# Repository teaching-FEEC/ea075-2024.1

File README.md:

# EA075 - Introdução ao Projeto de Sistemas Embarcados

1° semestre de 2024

Profa. Paula Dornhofer Paro Costa

⚠️ Não altere este arquivo README.MD

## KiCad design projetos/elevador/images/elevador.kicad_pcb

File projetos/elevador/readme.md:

# Projeto de um circuito de controle para elevadores
# Elevator control circuit project

## Apresentação

O presente projeto foi originado no contexto das atividades da disciplina de graduação *EA075 - Introdução ao Projeto de Sistemas Embarcados*, 
oferecida no primeiro semestre de 2024, na Unicamp, sob supervisão da Profa. Dra. Paula Dornhofer Paro Costa, do Departamento de Engenharia de Computação e Automação (DCA) da Faculdade de Engenharia Elétrica e de Computação (FEEC).

|Nome  | RA | Curso|
|--|--|--|
| André Guilherme da Luz  | 231343  | Eng. Elétrica|
| Gabriel Vianna Serra  | 258555  | Eng. Elétrica|

## Arquivos Importantes

Esquemático -- https://github.com/gaserra/ea075-2024.1/blob/636cf3e964390284290cc4d843cebd671a3fc66c/projetos/elevador/pdf/Esquem%C3%A1tico.pdf

Lista de Componentes -- https://github.com/gaserra/ea075-2024.1/blob/99e6916becb7f16d3520f543a689d3d09d11a9cd/projetos/elevador/componentes.md

PCB -- https://github.com/gaserra/ea075-2024.1/blob/31582293e5f1df663656b3f0aaa58bb34f14db0e/projetos/elevador/pdf/PCI.pdf

## Descrição do Projeto
A ideia do projeto consiste em desenvolver um circuito controlador para elevadores, a fim de tomar decisões como a escolha de que o elevador deve subir, descer ou manter-se no lugar com base no andar atual, prioridade de chamada e situações de segurança, por exemplo. Nosso contexto de concepção desse projeto veio do motivo de que é algo muito útil e presente no dia a dia de pessoas, bem como factível de ser projetado durante o semestre da disciplina, permitindo nos desafiar com as possíveis variáveis de desenvolvimento sem sobrecarregar os esforços dentro do tempo estipulado.

Outro lado positivo do projeto é que seu custo não tende a ser alto, levando em conta que a lógica pode ser desenvolvida sem a necessidade de processamento muito avançado, e os demais dispositivos que podem ser possivelmente usados não tendem a ser caros (alguns sensores e circuitos básicos para mudança de direção do motor). Dessa forma, levando em conta um investimento que requer pouca manutenção (o principal serviço é o software envolvido no controle dos elevadores e o microprocessador do mesmo, que tende a ter boa durabilidade), pouco capital e que proporciona um controle útil e necessário na logística dos elevadores, temos um projeto viável e de custo acessível.

O projeto consiste em um produto já estabelecido no mercado, que visa garantir um transporte vertical eficiente, seguro e confiável, ao mesmo tempo em que buscamos a redução dos custos. O sistema tende a beneficiar tanto prédios residenciais, ocorrendo uma valorização do imóvel, quanto comerciais, ocorrendo uma melhora da produtividade dos funcionários.

## Descrição Funcional

### Funcionalidades
O sistema de controle de elevadores deverá ser capaz de executar as seguintes tarefas:
  - Chamadas do elevador: receber e registrar chamadas de todos os andares do prédio.
  - Registrar as solicitações dentro do elevador.
  - Organizar as chamadas com base em uma fila de prioridade.
  - Gerenciar a abertura e fechamento das portas.
  - Responder imediatamente a situações de emergência.
  - Diagnosticar problemas mecânicos e elétricos.
  - Fornecer feedback aos passageiros sobre o andar que está.    

### Configurabilidade
O sistema possui os seguintes estados:
  - Subindo:
    O elevador está se deslocando para cima, pois recebeu uma chamada de algum andar mais elevado ou algum passageiro solicitou parada em um andar acima.
  - Descendo:
    O elevador está se deslocando para baixo, pois recebeu uma chamada de algum andar ou algum passageiro solicitou parada em um andar abaixo de sua posição.
  - Parado:
    O elevador está em um andar específico.
    - Portas abertas:
      O elevador está parado em um andar específico e com a porta aberta para entrada e saída de passageiros.
    - Portas fechadas:
      O elevador está parado em um andar com as portas fechadas, que ocorre após um tempo específico para entrada e saída dos passageiros e verificação de que não há passageiros se locomovendo pra dentro ou pra fora, bem como verificação de que não há possíveis falhas mecânicas e elétricas.

Ao receber chamadas de andares, o elevador (com portas fechadas) muda para o estado "subindo" ou "descendo", assim como quando o passageiro seleciona o andar desejado. Ao chegar no andar, o elevador muda para o modo "parado", inicialmente de portas fechadas, e rapidamente muda para o modo "portas abertas". Após um determinado tempo para entrarem e saírem passageiros, há a mudança de estado para "portas fechadas" novamente, se as condições de segurança forem satisfeitas. Assim, novas chamadas ocorrem, reiniciando. 
Há algumas mudanças de estado fora do funcionamento padrão. Ao verificar problemas mecânicos ou elétricos ou outras emergências, ele passa automaticamente para o modo "parado". Se está parado devido a problemas de segurança, suas portas podem permanecer abertas ou fechadas de acordo com a ocasião.

### Eventos
Os eventos de mudança de estado:
  - Chamada de um andar (evento não-periódico, passa do estado "parado" para "subindo" ou "descendo").
  - Chegada do elevador a um andar solicitado (evento não-periódico, passa do estado "subindo" ou "descendo" para "parado").
  - Ao parar, abertura das portas (evento não-periódico, passa do estado "parado" para o sub estado "portas abertas").
  - Fechamento das portas após um tempo para entrada e saída de passageiros, bem como garantia de segurança (evento não-periódico, passa do sub estado "portas abertas" para "portas fechadas").
  - Pressionamento do botão de fechada de portas (evento não-periódico, passa do estado "portas abertas" para "portas fechadas").
  - Pessoa entre a porta (evento não-periódico, mantém-se no sub estado "portas abertas").
  - Detecção de falha (evento não-periódico, passa do estado  "subindo" ou "descendo" para "parado").

### Tratamento de Eventos
  - Chamada de um andar:
    Ao receber uma chamada, o sistema deve organizar as chamadas da melhor maneira, de forma que não fique subindo e descendo várias vezes.
  - Chegada do elevador a um andar solicitado:
    Ao chegar em um andar, o sistema deve alinhar corretamente o chão do elevador com o andar.
  - Ao parar, abertura das portas:
    Após o alinhamento correto do chão do elevador e do andar, o sistema deve mandar um sinal para abertura da porta correta.
  - Fechamento das portas após um tempo para entrada e saída de passageiros:
    Após um tempo previamente definido de abertura das portas, o sistema deve enviar um sinal para o fechamento das portas se as condições de segurança forem satisfeitas.
  - Pressionamento do botão de fechada de portas:
    Caso esteja pressionado o botão, o sistema deve enviar um sinal para fechamento da porta.
  - Pessoa entre a porta:
    O sistema, ao detectar que há algo no local de fechamento da porta, deve enviar o sinal para manter a porta aberta ou cancelar o fechamento.
  - Detecção de falha:
    Ao detectar falha, o sistema deve interromper o movimento e ficar parado.

## Descrição Estrutural do Sistema
O sistema se baseia em um fluxo de estados onde definimos se um elevador sobe, desce ou se mantém parado com base nas solicitações internas e externas do elevador, bem como nas condições de segurança que devem ser satisfeitas. O diagrama abaixo retrata melhor os o fluxo de decisões:

Note que o mesmo funciona tanto para uma pessoa que solicita o elevador pelo lado de fora, quanto para alguém que aperta o botão de um andar já dentro do elevador. O diagrama mostra a situação em condições típicas e síncronas de funcionamento, mas haverá também a necessidade de uma verificação assíncrona em casos de falhas durante o trajeto do elevador, onde o mesmo deve parar e acionar suporte/segurança.
A fila também tem um papel importante, conforme explicado na sessão "Especificação de algoritmos", para saber se o elevador sobe ou desce de acordo com a ordem apertada e se para ou não em outro andar no caminho. De forma resumida, após alguma solicitação que entra em uma fila com uma determinada prioridade, a ideia é que o elevador se movimente baseado nessa fila para atender aos chamados.

## Especificações 

### Especificação Estrutural

O projeto possui dois atuadores, ambos motores CC, para controle de abertura e fechamento das portas do elevador e para subir e descer a cabine. O motor utilizado para o deslocamento vertical da cabine apresenta bastante torque, portanto, sua potência é alta. Com isso, a alimentação é feita utilizando um conversor AC/DC RAC20-K, que entrega 48V para alimentação do circuito do motor. O controle do sentido e da velocidade  é feito na saída do retificador utilizando uma ponte H L298N, conectada também ao microcontrolador, que consegue fazer o controle de ambos os motores paralelamente. 

A ideia do controle da parada correta da cabine do elevador é utilizar dois sensores fotoelétricos em cada andar (um para a parte inferior do piso e outro para a parte superior), sendo que o modelo em consideração é o E3Z-F da Omron. Assim, ao passar pelo sensor, o sistema saberá em que andar está a cabine e o momento correto para iniciar a frenagem. Outra importante função desse periférico é estacionar a cabine de forma extremamente precisa, alinhando o piso do elevador com o andar. Com as informações do andar, um display de sete seguimentos mostrará ao passageiro o andar que a cabine está, o modelo utilizado é o D1X8K-14BL. Os dados são enviados como dois bits, que são decodificados pelo 74LS48, e em seguida enviados para o display.

A porta possui quatro sensores de infravermelho, sendo utilizados dois para cada altura pré-determinada, dispostos em ambos os lados da porta. O papel desses sensores é detectar se há algum objeto entre as portas. O modelo escolhido foi o E18-D80NK-N, que possui um alcance de 6 a 80 cm. Quando um objeto for detectado, o sensor envia ao microcontrolador um sinal de nível lógico baixo. Com a leitura do nível lógico, um comando é enviado para o motor manter a porta aberta.

O elevador irá se locomover por quatro andares, assim, teremos quatro push buttons dentro do elevador para o passageiro indicar o destino desejado. Cada andar possuirá um push button para chamar o veículo. Logo, teremos oito no sistema, que, ao serem pressionados, enviam um sinal que será armazenado na memória estruturada em pilha. Na seção de especificação do algoritmo, o modo de funcionamento dos chamados é explicado de forma a otimizar o trajeto do elevador. Cada push bottom será conectado à uma porta GPIO do microcontrolador.

O microcontrolador escolhido para o sistema foi RP2040 desenvolvido pela Raspbarry Pi. A escolha ocorreu devido à quantidade de portas necessárias para todo o controle do sistema, e como o projeto não precisa uma compexidade alta, este microcontrolador atende os requisitos, além de possuir um custo acessível. Para a comunicação serial, a comunicação do tipo I2C foi escolhida, pois não há necessidade de uma alta velocidade de comunicação que vença em detrimento da menor complexidade.

### Especificação de Algoritmos 
Para a gestão de fila dos andares, o projeto se baseia no seguinte fluxograma:

Os eventos relacionados à abertura e ao fechamento de portas, bem como detecção de falha, sobrecarga e pessoa entre as portas são tratados no fluxograma da seção "_Descrição Estrutural do Sistema_", e tais eventos se relacionam diretamente com este acima no que resumimos pela tomada de decisão "Verificações de segurança ok?". Dessa forma, o algoritmo como um todo deve tratar dos dois fluxogramas, sendo que o primeiro diagrama se encaixa dentro do segundo para simplificarmos a visualização.

O microcontrolador apresenta memórias integradas, ROM, Flash e SRAM, que trabalham com palavras de 32 bits. Visto que projetaremos um controle para elevadores com até 4 andares (suficientemente representados por 2 bits), usando 2 sensores de nível por andar (mais 8 bits para monitoramento), e outras funções de controle como abertura das portas, detecção de movimento, etc, estimamos que seria necessário em torno de 16 bits para tal, portanto o microcontrolador satisfaz a demanda, não necessitando da utilização de uma memnória externa.

## Referências
http://www.electrical-knowhow.com/2012/04/elevator-control-system.html

http://fpgaparatodos.com.br/2011/08/04/exemplo-de-exemplo/

https://cpi.com.ar/info_productos/pdf/E3Z-F.pdf

https://www.watelectronics.com/e18-d80nk-adjustable-infrared-sensor/

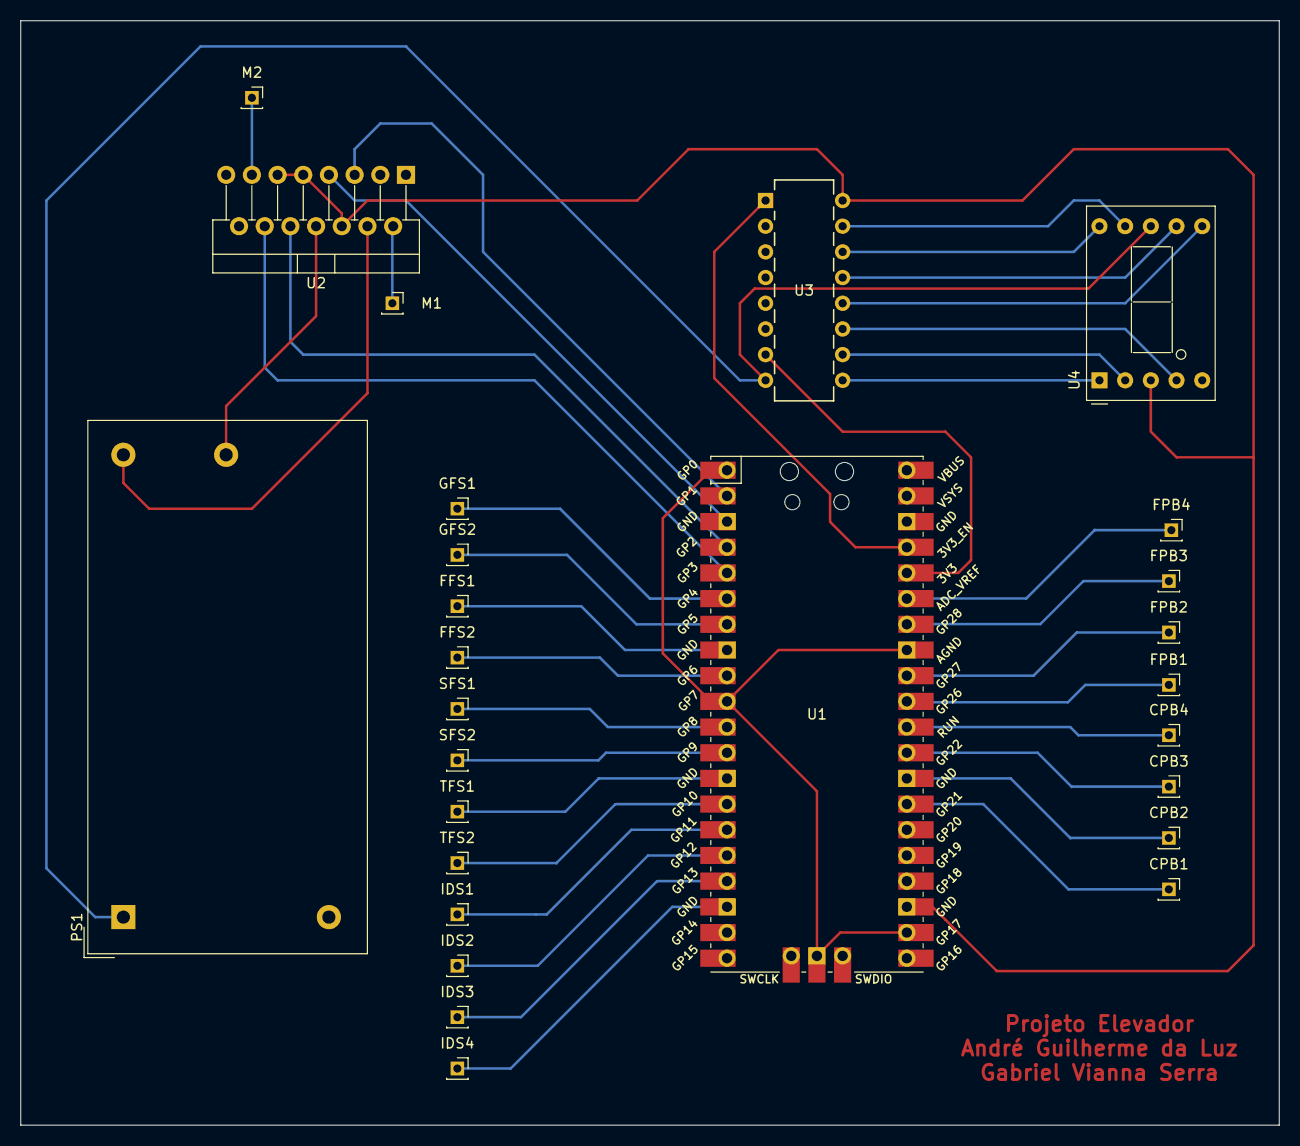
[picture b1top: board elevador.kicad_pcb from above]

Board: 2 copper layers, 124.5 x 109.2 mm, 27 parts (0 on the bottom side), 40 nets.

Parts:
CPB1: Cabin P/B 0; PinSocket_1x01_P2.00mm_Vertical
CPB2: Cabin P/B 1; PinSocket_1x01_P2.00mm_Vertical
CPB3: Cabin P/B 2; PinSocket_1x01_P2.00mm_Vertical
CPB4: Cabin P/B 3; PinSocket_1x01_P2.00mm_Vertical
FFS1: First Floor Sensor 1; PinSocket_1x01_P2.00mm_Vertical
FFS2: First Floor Sensor 2; PinSocket_1x01_P2.00mm_Vertical
FPB1: Floor P/B 0; PinSocket_1x01_P2.00mm_Vertical
FPB2: Floor P/B 1; PinSocket_1x01_P2.00mm_Vertical
FPB3: Floor P/B 2; PinSocket_1x01_P2.00mm_Vertical
FPB4: Floor P/B 3; PinSocket_1x01_P2.00mm_Vertical
GFS1: Ground Floor Sensor 1; PinSocket_1x01_P2.00mm_Vertical
GFS2: Ground Floor Sensor 2; PinSocket_1x01_P2.00mm_Vertical
IDS1: Infrared Door Sensor 1; PinSocket_1x01_P2.00mm_Vertical
IDS2: Infrared Door Sensor 2; PinSocket_1x01_P2.00mm_Vertical
IDS3: Infrared Door Sensor 3; PinSocket_1x01_P2.00mm_Vertical
IDS4: Infrared Door Sensor 4; PinSocket_1x01_P2.00mm_Vertical
M1, M2: Motor_DC; PinSocket_1x01_P2.00mm_Vertical
PS1: RAC20-48SK; Converter_ACDC_Recom_RAC20-xxSK_THT
SFS1: Second Floor Sensor 1; PinSocket_1x01_P2.00mm_Vertical
SFS2: Second Floor Sensor 2; PinSocket_1x01_P2.00mm_Vertical
TFS1: Third Floor Sensor 1; PinSocket_1x01_P2.00mm_Vertical
TFS2: Third Floor Sensor 2; PinSocket_1x01_P2.00mm_Vertical
U1: RP2040; RPi_Pico_SMD_TH
U2: L298N; TO-220-15_P2.54x2.54mm_StaggerOdd_Lead4.58mm_Vertical
U3: 74LS48; DIP16_300_TEX
U4: D1X8K-14BL; D1X8K

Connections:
GND: PS1.1 (AC(N)), U3.8 (GND), U4.8 (CC)
unnamed: M1.1 (+), U2.2 (OUT1)
unnamed: M2.1 (+), U2.13 (OUT3)
unnamed: PS1.4 (-Vout), U2.8 (GND)
unnamed: PS1.5 (+Vout), U2.4 (Vs)
unnamed: U1.1 (IOVDD), U1.10 (IOVDD), U1.22 (IOVDD), U1.33 (IOVDD), U1.42 (IOVDD)
unnamed: U1.2 (GPIO0), U2.5 (IN1)
unnamed: U1.3 (GPIO1), U2.7 (IN2)
unnamed: U1.4 (GPIO2), U2.10 (IN3)
unnamed: U1.5 (GPIO3), U2.12 (IN4)
unnamed: GFS1.1, U1.6 (GPIO4)
unnamed: GFS2.1, U1.7 (GPIO5)
unnamed: FFS1.1, U1.8 (GPIO6)
unnamed: FFS2.1, U1.9 (GPIO7)
unnamed: SFS1.1, U1.11 (GPIO8)
unnamed: SFS2.1, U1.12 (GPIO9)
unnamed: TFS1.1, U1.13 (GPIO10)
unnamed: TFS2.1, U1.14 (GPIO11)
unnamed: IDS1.1, U1.15 (GPIO12)
unnamed: IDS2.1, U1.16 (GPIO13)
unnamed: IDS3.1, U1.17 (GPIO14)
unnamed: IDS4.1, U1.18 (GPIO15)
unnamed: CPB1.1, U1.27 (GPIO16)
unnamed: CPB2.1, U1.28 (GPIO17)
unnamed: CPB3.1, U1.29 (GPIO18)
unnamed: CPB4.1, U1.30 (GPIO19)
unnamed: FPB1.1, U1.31 (GPIO20)
unnamed: FPB2.1, U1.32 (GPIO21)
unnamed: FPB3.1, U1.34 (GPIO22)
unnamed: FPB4.1, U1.35 (GPIO23)
unnamed: U1.36 (GPIO24), U3.7 (A)
unnamed: U1.37 (GPIO25), U3.1 (B)
unnamed: U3.9 (e), U4.1 (E)
unnamed: U3.10 (d), U4.2 (D)
unnamed: U3.11 (c), U4.4 (C)
unnamed: U3.12 (b), U4.6 (B)
unnamed: U3.13 (a), U4.7 (A)
unnamed: U3.14 (g), U4.10 (G)
unnamed: U3.15 (f), U4.9 (F)
VCC: U1.23 (DVDD), U2.6 (EnA), U2.9 (Vss), U2.11 (EnB), U3.16 (VCC), U4.3 (CC)

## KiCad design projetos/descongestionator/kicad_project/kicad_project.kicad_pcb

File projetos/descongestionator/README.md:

# `Rodovias Fluidas: Sistema de Redução de Congestionamentos`
# `Smooth Highways: Trafic Jam Reduction System`

## Apresentação

O presente projeto foi originado no contexto das atividades da disciplina de graduação *EA075 - Introdução ao Projeto de Sistemas Embarcados*, 
oferecida no primeiro semestre de 2024, na Unicamp, sob supervisão da Profa. Dra. Paula Dornhofer Paro Costa, do Departamento de Engenharia de Computação e Automação (DCA) da Faculdade de Engenharia Elétrica e de Computação (FEEC).

 |Nome  | RA | Curso|
 |--|--|--|
 | Kevin Caio Marques dos Santos  | 247218  | Eng. de Computação|
 | Thiago Maximo Pavão  | 247381  | Eng. de Computação|

## Descrição do Projeto

O projeto foi idealizado para abordar um problema comum enfrentado pelos motoristas hoje em dia: congestionamentos em rodovias. Muitas vezes, atribui-se esse problema à ocorrência de acidentes que bloqueiam uma das vias, forçando o tráfego a se concentrar na outra via. No entanto, em muitos casos de congestionamento, não há acidente aparente ou outra explicação clara, o que levanta questões para os motoristas mais perspicazes.

Durante uma investigação sobre essa questão, foi encontrado um [vídeo](https://www.youtube.com/watch?v=iHzzSao6ypE) que explicava a causa de muitos congestionamentos. O principal fator identificado foi a grande disparidade de velocidades entre os veículos na mesma via, juntamente com ultrapassagens realizadas por veículos mais lentos. Isso faz com que outros motoristas tenham que reduzir sua velocidade, criando uma espécie de "onda de lentidão" que se propaga ao longo da rodovia. Eventualmente, essa onda de lentidão pode levar alguns carros a pararem completamente para evitar colisões.

Diante desse contexto, o objetivo do projeto é reduzir a propagação dessa onda de lentidão, diminuindo assim a extensão dos congestionamentos, especialmente nos pontos onde os motoristas são obrigados a parar completamente. O objetivo final é evitar que o congestionamento se agrave.

A prejudicialidade dos congestionamentos está muito além do atraso que gera para os motoristas em suas trajetórias diárias. Alguns exemplos de consequências são:

 - Estresse dos motoristas
 - Acidentes
 - Maior consumo de combustível
 - Maior poluição
 - Maior prejuízo para a saúde dos motoristas expostos a poluição gerada pelos carros

Nesse sentido, o Rodovias Fluídas® visa solucionar todos esses problemas ao monitorar o surgindo desses engarrafamentos e enviar informações aos motoristas que vem atrás para reduzirem a velocidade, de modo ao chegarem ao local do suposto congestionamento, ele ja tenha desaparecido. Com a implementação desse sistema, prevê-se que haja um significativo retorno econômico ao reduzir o consumo de combustível e a prevenção de acidentes.

## Descrição Funcional

O objetivo do projeto é identificar congestionamentos nas rodovias e avisar os motoristas que trafegam na mesma rodovia para reduzirem a velocidade, de modo que ao chegarem ao local em que existia o engarrafamento ele já tenha se resolvido.

### Funcionalidades

- Medir a velocidade do veículo
- Medir a posição do veículo na rodovia
- Mostrar mensagens em um display sobre congestionamentos e informar qual velocidade o motorista deve trafegar.
- Reproduzir avisos sonoros quando novas informações estão disponíveis
- Detectar a localização e o tamanho de congestionamentos
- Determinar a velocidade adequada em reação a um congestionamento à frente
- Capacidade de distribuição das informações sobre congestionamentos para os carros trafegando na rodovia 

### Configurabilidade

Como configuração, o usuário que possuir o dispositivo em seu carro pode optar por desabilitar o aviso sonoro e ao invés disso o display de informações deve piscar algumas vezes para chamar a atenção do motorista.

### Eventos

#### Módulo Móvel

1. Inicialização do sistema
2. Conexão do Módulo com uma torre dentro do seu alcance
3. Monitoramento da velocidade do veículo (periódico, 3 segundos)
4. Falha na comunicação com os periféricos
5. Recebimento de informações da torre
6. Perda de conexão com a torre

#### Módulo Fixo (Torre)

1. Inicialização do sistema
2. Nova conexão com um carro
3. Fim de uma conexão com um carro
4. Recebimento de dados (posição, direção e velocidade) de um carro
5. Notificação de condição de tráfego por outras torres
6. Atualização nas condições de tráfego da via (por algoritmo interno)

### Tratamento de Eventos

#### Módulo Móvel

1. Inicializa todos os periféricos e verifica por erros
2. Mostra a mensagem de conectado no visor lcd e inicializa um timer
3. Coleta a velocidade do veículo e compara com a última velocidade enviada a torre, se essa diferença for maior que um limite, envia as informações atuais de velocidade, direção e posição para a torre, e atualiza a última velocidade enviada para a atual
4. Para o timer, encerra a conexão com a torre se houver e mostra uma mensagem de erro no visor lcd se o erro não for no visor
5. Verifica a mensagem recebida, se for de congestionamento, mostra no visor a mensagem de cosgestionamento e a velocidade maxima fornecida pela torre, se não for de congestionamento apenas mostra a velocidade máxima recebida. Além disso, se a velocidade máxima recebida for diferente da última recebida, emite um alerta sonoro
6. Mostra a mensagem de disconectado no visor e para o timer 

#### Módulo Fixo (Torre)

1. Cria estruturas de dados para armazenamento das informações recebidas pelos carros e outras torres. Além disso, se conecta com as outras torres.
2. Informa a velocidade máxima da via, e cria entrada na tabela para armazenar dados enviados pelo carro.
3. Remove a entrada na tabela do carro desconectado.
4. Calcula a posição em que o carro se encontra na rodovia (o kilômetro) e atualiza os dados na tabela na posição relativa ao carro que gerou o evento.
5. Atualiza tabela de informações enviadas por outras torres. E propaga as informações recebidas para a torre vizinha.
6. Envia cada carro a velocidade que ele deve trafegar, avisando também se um congestionamento foi detectado. Além dos carros, avisa também torres vizinhas sobre as novas condições.

## Descrição Estrutural do Sistema

O sistema será composto por dois tipos de dispositivos: Módulos móveis, que estão presentes nos carros dos usuários do sistema e módulos fixos, presentes ao longo das rodovias, principalmente em trechos em que congestionamentos são comuns.

Os módulos móveis tem como objetivo monitorar a velocidade do carro e informar ao motorista quando deve reduzir sua velocidade. Ele baseia essa decisão em sinais recebidos pelo módulos fixo mais próximo. Além disso, tem o papel de informar a velocidade do carro para o módulo fixo mais próximo.

Os dispostivos fixos são torres colocadas ao longo da via, e tem como objetivo detectar congestionamentos, recebendo informações de velocidade dos motoristas mais próximos, e repassar a informação para torres anteriores na via, que por sua vez avisam sobre as condições ao módulos móveis proxímos a elas.

## Especificações

### Especificação Estrutural

A realização do projeto completo só é possível com a definição da forma de comunicação entre os dispositivos, as torres (módulo fixo) precisam ser capazes de realizar conexão com todos os carros em seu alcance e também com torres vizinhas. Para simplificar o projeto, nos limitamos a pesquisar algumas tecnlogias existentes ou em desenvolvimento que possam ser utilizadas para realizar essa comunicação, e portanto não especificamos aqui componentes nem os algoritmos necessários para tornar essa comunicação possível.

#### Módulo móvel

Tabela de periféricos escolhidos

| Nome | Interface | Links | Motivo | Custo |
|--|--|--|--|--|
| Display | I2C | [produto](https://curtocircuito.com.br/display-lcd-16x2-backlight-azul-i2c.html?srsltid=AfmBOorUBvmO1sjFAtLiMtKyeGpYR1-XtbEsuhcUkG65ZfNAgPfHhxg7naQ) [datasheet](https://www.handsontec.com/dataspecs/module/I2C_1602_LCD.pdf) | Menor display que atende as mensagens que deseja-se mostrar e com menor custo, quando comparado a displays OLED, por exemplo. | R$ 25 |
| Buzzer ativo | GPIO | [produto](https://www.mercadolivre.com.br/3x-buzzer-ativo-5v-sinal-beep-arduino-raspberry-som/p/MLB32625316?matt_tool=18956390&utm_source=google_shopping&utm_medium=organic&item_id=MLB4440875150&from=gshop) | Apenas para realizar um aviso simples, buzzer ativo para não precisar gerar uma onda como entrada | R$ 3 |
| GPS | I2C | [produto](https://pt.aliexpress.com/item/1005001325488063.html?spm=a2g0o.productlist.main.21.16bf6D4k6D4kkE&algo_pvid=ee1dfcd7-d9ed-4cb6-a019-f2d89ec01ed2&algo_exp_id=ee1dfcd7-d9ed-4cb6-a019-f2d89ec01ed2-10&pdp_npi=4%40dis%21BRL%2118.12%2118.12%21%21%213.38%213.38%21%402103252b17163011627366297e1daf%2112000015698279168%21sea%21BR%210%21AB&curPageLogUid=ytOUFtU2BXcg&utparam-url=scene%3Asearch%7Cquery_from%3A) [datasheet](https://content.u-blox.com/sites/default/files/products/documents/NEO-6_DataSheet_%28GPS.G6-HW-09005%29.pdf) | Dispositivo simples de GPS e com precisão suficiente para o projeto, existem variações na família porém a de pior velocidade e resolução já excede o que é necessário para o projeto. | R$ 20 |
| Bússula de três eixos | I2C | [produto](https://pt.aliexpress.com/item/1005006291063452.html?spm=a2g0o.productlist.main.1.dc4evlYHvlYHY3&algo_pvid=c34535e0-7379-445e-bfe4-024fbe78167f&algo_exp_id=c34535e0-7379-445e-bfe4-024fbe78167f-0&pdp_npi=4%40dis%21BRL%2126.79%214.99%21%21%2136.19%216.74%21%402103248517163012654687965e29ec%2112000036755638743%21sea%21BR%210%21AB&curPageLogUid=qAsI2Sp9r1qq&utparam-url=scene%3Asearch%7Cquery_from%3A) [datasheet](https://pdf1.alldatasheet.com/datasheet-pdf/download/428790/HONEYWELL/HMC5883L.html) | Baixo custo e precisão suficiente para que a torre seja capaz de distinguir entre as duas direções da pista. | R$ 5 |
| ELM327 | USB | [produto](https://pt.aliexpress.com/item/1005004078281314.html?src=google&albch=shopping&acnt=768-202-3196&slnk=&plac=&mtctp=&albbt=Google_7_shopping&isSmbAutoCall=false&needSmbHouyi=false&albcp=17364768653&albag=&trgt=&crea=pt1005004078281314&netw=x&device=c&albpg=&albpd=pt1005004078281314&gad_source=1&aff_fcid=ab8340a8c4924522a2f60389e0a5a9b5-1716303063740-03722-UneMJZVf&aff_fsk=UneMJZVf&aff_platform=aaf&sk=UneMJZVf&aff_trace_key=ab8340a8c4924522a2f60389e0a5a9b5-1716303063740-03722-UneMJZVf&terminal_id=8d6b63a746384503a8028a560225b27e&afSmartRedirect=y) | Dispositivo mais comum para este tipo de interface com o carro pela porta ODB | R$ 20 |

Ainda é necessário definir um circuito integrado para realizar a conversão de USB para UART

Escolha da MCU:

Dos algoritmos especificados, vemos que este módulo exige baixa memória e pouca capacidade de processamento, porque a MCU é apenas responsável por intermediar os periféricos com as torres. Desta forma, encontramos a família de microcontroladoras de 8 bits ATtinyXXX.

link do datasheet: https://ww1.microchip.com/downloads/aemDocuments/documents/MCU08/ProductDocuments/DataSheets/ATtiny202-04-402-04-06-Auto-DataSheet-DS40002159A.pdf

Analisando entre as variações, a escolha deve ser feita com base no número de pinos e da quantidade de memória Flash/RAM. A versão com menos (8) pinos não disponibiliza nenhum pino multiplexável para I2C, e portanto não pode ser utilizada. Isto pode ser visto nas imagens abaixo, os pinos SDA e SCL são multiplexáveis apenas nos pinos PB0 e PB1, que não estão disponíveis nessa versão.

Pinagem das versões com 8 e 14 pinos

Tabela de multiplexação dos pinos

Já a versão de 14 pinos possibilita que sejam acessados os módulos USART, I2C e GPIO, que completa as interfaces necessárias. Quanto à memória, de acordo com nossas estimativas, a versão com 128 B de RAM e 2 kB de memória Flash deve ser suficiente. Portanto, definimos a microcontroladora ATtiny204, que tem um custo de apenas R$ 3. 

#### Módulo fixo

Para simplificação do projeto, optou-se por focar na especificação do módulo móvel, e portanto não foram escolhidos precisamente os componentes e placa micro controladora para o módulo fixo. 

No entanto, foi percebido que a especificação dos algoritmos de tratamento de eventos neste módulo seria importante para um bom entendimento da dinâmica do projeto e do fluxo de informações, então eles foram feitos e podem ser vistos abaixo.

Além disso, algumas restrições de memória e de processamento foram comentadas, o que guiaria a escolha de componentes para este módulo: Processador, memória RAM, memória de programa e memória de dados.

### Especificação de Algoritmos 

Como já explicado, não realizamos a especificação do circuito utilizado para possibilitar a comunicação entre os módulos, mas supomos aqui que qualquer tecnologia utilizada seja capaz de gerar os seguintes eventos: conexão de um novo dispositivo, perca da conexão, recebimento de dados e envio de dados. Apenas supondo estes princípios de inter-comunicação foram gerados os algoritmos mostrados a seguir. 

#### Algoritmos do módulo móvel

```
// Evento 1: Ao inicializar
function setup() {
  status = initLCD();
  if(status == ERROR) {
    errorBeep();
    stop();
  }
  
  status = initGPS();
  if(status == ERROR) {
    showMessageLCD(INTERNAL_ERROR);
    errorBeep();
    stop();
  }

  status = initCompass();
  if(status == ERROR) {
    showMessageLCD(INTERNAL_ERROR);
    errorBeep();
    stop();
  }

  status = initCarCommunication();
  if(status == ERROR) {
    showMessageLCD(CAR_COMM_ERROR);
    errorBeep();
    stop();
  }
}

// Evento 2: Quando entra no alcance de uma torre, e se conecta a ela
function onConnect() {
  showMessageLCD(CONNECTED);
  startTimer();
}

// Evento 3: Quando o timer reinicia, curto período para detectar grandes variações na velocidade e notificar a torre
function timerInterrupt() {
  velocity = getCarVelocity();

  if(abs(velocity - lastSentVelocity) > TRESHOLD * velocity  or  currentTime - lastSentTime > MAX_PERIOD) {
    lastSentVelocity = velocity;
    gpsData = readGPS();
    compassData = readCompass();

    sendData(velocity, gpsData, compassData);
  }
}

// Evento 4: Ao ocorrer um erro de conexão com algum periferico, mostra mensagem de erro, se possível, e finaliza conexao com torre se necessário
function peripheralError(errorMessage){
  if(errorMessage != commTower){
     stopConnection();
  }
  if(errorMessage != commLCD) {
     showMessageLCD(DISCONNECTED);
  }
  errorBeep();
  stop();
}

// Evento 5: Ao receber um dado da torre. Informação sobre a velocidade máxima a se andar e se há congestionamento à frente
function receiveData(reponse) {
  if(response.trafficJam == True) {
    showMessageLCD(TRAFFIC_JAM, response.maxVelocity);
  }
  else {
    showMessageLCD(CONNECTED, response.maxVelocity);
  }

  if(lastMaxVelocity != response.maxVelocity) {
    alertBeep();
    lastMaxVelocity = response.maxVelocity;
  }
}

// Evento 6: Ao sair do alcance da torre
function onDisconnect() {
  showMessageLCD(DISCONNECTED);
  stopTimer();
}
```
Para este módulo não há grande necessidade de memória ram, será preciso armazenar temporariamente as informações de velocidade atual, velocidade enviada anteriormente, posição atual do veículo, direção de movimento, tempo de máquina atual e último tempo de máquina de envio. Além de pequenas informações informações de status e retornos de funções, porém tais variáveis serão apenas alguns bytes e por hora não serão contabilizadas, só serão levadas em consideração durante a estimativa final, a qual considerará uma quantidade a mais de armazenamento para englobar tais variáveis. Para as informações maiores, segue abaixo a análise de tamanho para cada variável:

- Velocidade atual: de 0 - 120 km/h com precisão de 5 km/h, temos 24 possibilidades, que necessita de 5 bits.
- Velocidade enviada anteriormente: de 0 - 120 km/h com precisão de 5 km/h, temos 24 possibilidades, que necessita de 5 bits.
- Posição: informações de latitudade e longitude recebidas pelo módulo de gps, ambas variáveis float, de 32 bits cada, 64 bits no total. 
- Direção: recebida pela bússola, informações de magnetude nos eixos x, y e z, a serem usadas para cálculos posteriores, todas essas informações possuem tamanho de 2 bytes cada, totalizando 48 bits.
- Tempo de máquina atual: fornecido pelo timer interno de execução do programa na MCU, variável de tipo int, 32 bits.
- Último tempo de máquina de envio: fornecido pelo timer interno de execução do programa na MCU, variável de tipo int, 32 bits. 

Realizando a soma de todos esses tamanhos, temos que o total de bits necessários para armazenar tais variáveis na memória ram é de: 5 + 5 + 64 + 48 + 32 + 32 = 186 bits ~ 25 bytes
O valor de bytes foi arredondado para cima, de modo a englobar aquelas outras variáveis comentadas anteriormente.

Além disso, será necessário armazenar as mensagens que serão mostradas no display lcd, tais mensagens serão armazenadas em uma memória flash, pois toda vez que ligar o sistema as mensagens que podem ser exibidas serão as mesmas, portanto necessitam ser armazenada em uma memória não volátil. Segue abaixo as frases e os cálculos de tamnanhos de armazenamento:

Mensagens mostradas em operação normal:

Primeira Linha do display:
  - "Conectado": temos 9 caracteres, mais 1 caractere do '\0' no final da string, cada caractere de 1 byte, totalizando 10 bytes.  
  - "Desconectado": temos 12 caracteres, mais 1 caractere do '\0' no final da string, cada caractere de 1 byte, totalizando 13 bytes.   
  - "Congestionamento": temos 16 caracteres, mais 1 caractere do '\0' no final da string, cada caractere de 1 byte, totalizando 17 bytes.
    
Segunda Linha do display:	
  - "Vmax: xxx km/h": temos 14 caracteres, mais 1 caractere do '\0' no final da string, cada caractere de 1 byte, totalizando 15 bytes.
    
Mensagens mostradas em eventos de erros:

Primeira Linha do display:
  - "Erro": temos 4 caracteres, mais 1 caractere do '\0' no final da string, cada caractere de 1 byte, totalizando 5 bytes.  
  - "Erro Interno": temos 12 caracteres, mais 1 caractere do '\0' no final da string, cada caractere de 1 byte, totalizando 13 bytes.
    
Segunda Linha do display:
  - "conexão carro": temos 13 caracteres, cada caractere de 1 byte, totalizando 14 bytes.  
  - "tente reiniciar": temos 15 caracteres, cada caractere de 1 byte, totalizando 16 bytes.  

Somando todos esses valores, temos que o total de bytes necessários para armazenar essas mensagens é de 103 bytes. 
Para o cálculo do tamanho da memória flash, temos que ela precisa ser de no mínimo 103 bytes, para armazenar pelo menos todas as mensagens a serem exibidas. Para armazenar todo o programa estima-se que necessitará na ordem de centenas de bytes. 

#### Algoritmos do módulo fixo

```
// Evento 1: Ao inicializar
function setup() {
  initCarsInfoTable();
  initTowersInfoTable();

  connectNeighboringTowers();
}

// Evento 2: Carro se conecta à torre ao entrar em seu alcance
function onCarConnect(car) {
  addEntryOnCarTable(car);
  car.sendData(ROAD_MAX_VELOCITY);
}

// Evento 3: Recebimento de dados (posição, direção e velocidade) de um carro
function receiveCarData(data) {
  roadPosition = calculateCarPositionOnRoad(data.position);
  updateEntryOnCarTable(roadPosition, data.direction, data.speed);
}

// Evento 4: Carro se desconecta da torre (fora do range)
function onCarDisconnect(car) {
  removeEntryFromCarTable(car);
}

// Evento 5: Ao receber mensagens de outras torres com atualizações
function onTrafficConditionNotification(trafficCondition) {
  updateTowerTable(trafficCondition);
  propagateNotification();
}

// Evento 6: Ao detectar internamente uma atualização nas condições de tráfego
function onTrafficConditionUpdate(trafficCondition) {
  for(car in table) {
    maxVelocity = calculateMaxVelocity(car.position, car.direction, trafficCondition);
    car.sendData(TRAFFIC_JAM, maxVelocity);
  }

  notifyNeighboringTowers(trafficCondition);
}
```

A lógica mais complexa do programa está na função de análise dos dados coletados dos carros e informações recebidas das outras torres, a ideia é que essa análise seja feita continuamente em segundo plano por algum algoritmo potencialmente sofisticado. Uma possibilidade é que isso fosse feito por algum algoritmo de inteligência artificial, mas isso traz a necessidade de um processador mais poderoso. Também poderia ser interessante utilizar um processador com mais de um núcleo, para que as tarefas de comunicação com os veículos e com as outras torres (e outras tarefas acopladas à estas) possam ser feitas de forma independente da análise dos dados em tempo real, sem interromper o algoritmo de análise.

Uma análise de memória que pode ser feita a partir dos algoritmos mostrados é a seguinte. Temos duas tabelas de dados que devem ser armazenadas na memória RAM, o tamanho máximo de cada uma delas depende da quantidade de carros suportada por cada torre e da quantidade de informações relativas à outras torres que cada uma armazenará.

Supondo que 

- Cada torre tenha um alcance de 1 km
- Para o algoritmo de prevenção de congestionamento seja necessário ter as informações de tráfego de 21 km à frente
- Cada torre suporte atender 250 carros

A tabela de informações das torres terá portanto conhecimento de um total de 21 km * 2 = 42 km (bidirecional) e então cada torre precisa se comunicar e armazenar informações de outras 20.
Supondo que o pacote de informações de cada uma seja de 10 bytes, detalhando bem o estado do tráfego precisariamos de 20 * 10 = 200 bytes de memória RAM para essa tabela.

Sobre cada carro conectado, a torre deve armazenar informações sobre sua posição, velocidade e direção e portanto a quantidade de bits para cada carro é dada por

- Posição: especificar em um espaço de 2 km, com precisão de 100m, temos 20 possibilidades, necessitando de 5 bits.
- Velocidade: de 0 - 120 km/h com precisão de 5 km/h, temos 24 possibilidades, que necessita de 5 bits.
- Direção: O carro pode estar andando apenas em um dos dois sentidos na via, portanto é apenas necessário um bit.

Isso totaliza 11 bits por carro, e portanto 2750 bits ~ 344 bytes.

Além disso, cada torre precisa armazenar um mapa para conseguir associar a posição dada pelo GPS de cada módulo móvel à uma posição na pista (o kilômetro da posição, por exemplo).

O mapa das torres pode ser representado como uma lista de coordenadas e o kilômetro equivalente para a coordenada em questão. Considerando 4 bytes para longitude e latitude, mais 5 bits para especificação da posição relativa ao alcance da torre. Temos então 69 bits por linha, o que totaliza aproximadamente 173 bytes.

Sobre memória de programa, temos algo muito maior do que o caso do módulo móvel. O algoritmo de análise de dados e a função de determinação da posição do carro na rodovia são provavelmente os maiores ocupantes deste tipo de memória, por serem lógicas mais complexas. Estima-se que seja necessário uma memória de programa na ordem de kilo bytes ou dezenas de kilo bytes.

Um resumo dos requisitos de memória do sistema são então

- Memória RAM: 600 B
- Memória de dados (mapa, ROM): 200 B
- Memória de programa (ROM ou Flash): ~ 10 kB

## Referências

- Vídeo motivador do projeto: https://www.youtube.com/watch?v=iHzzSao6ypE

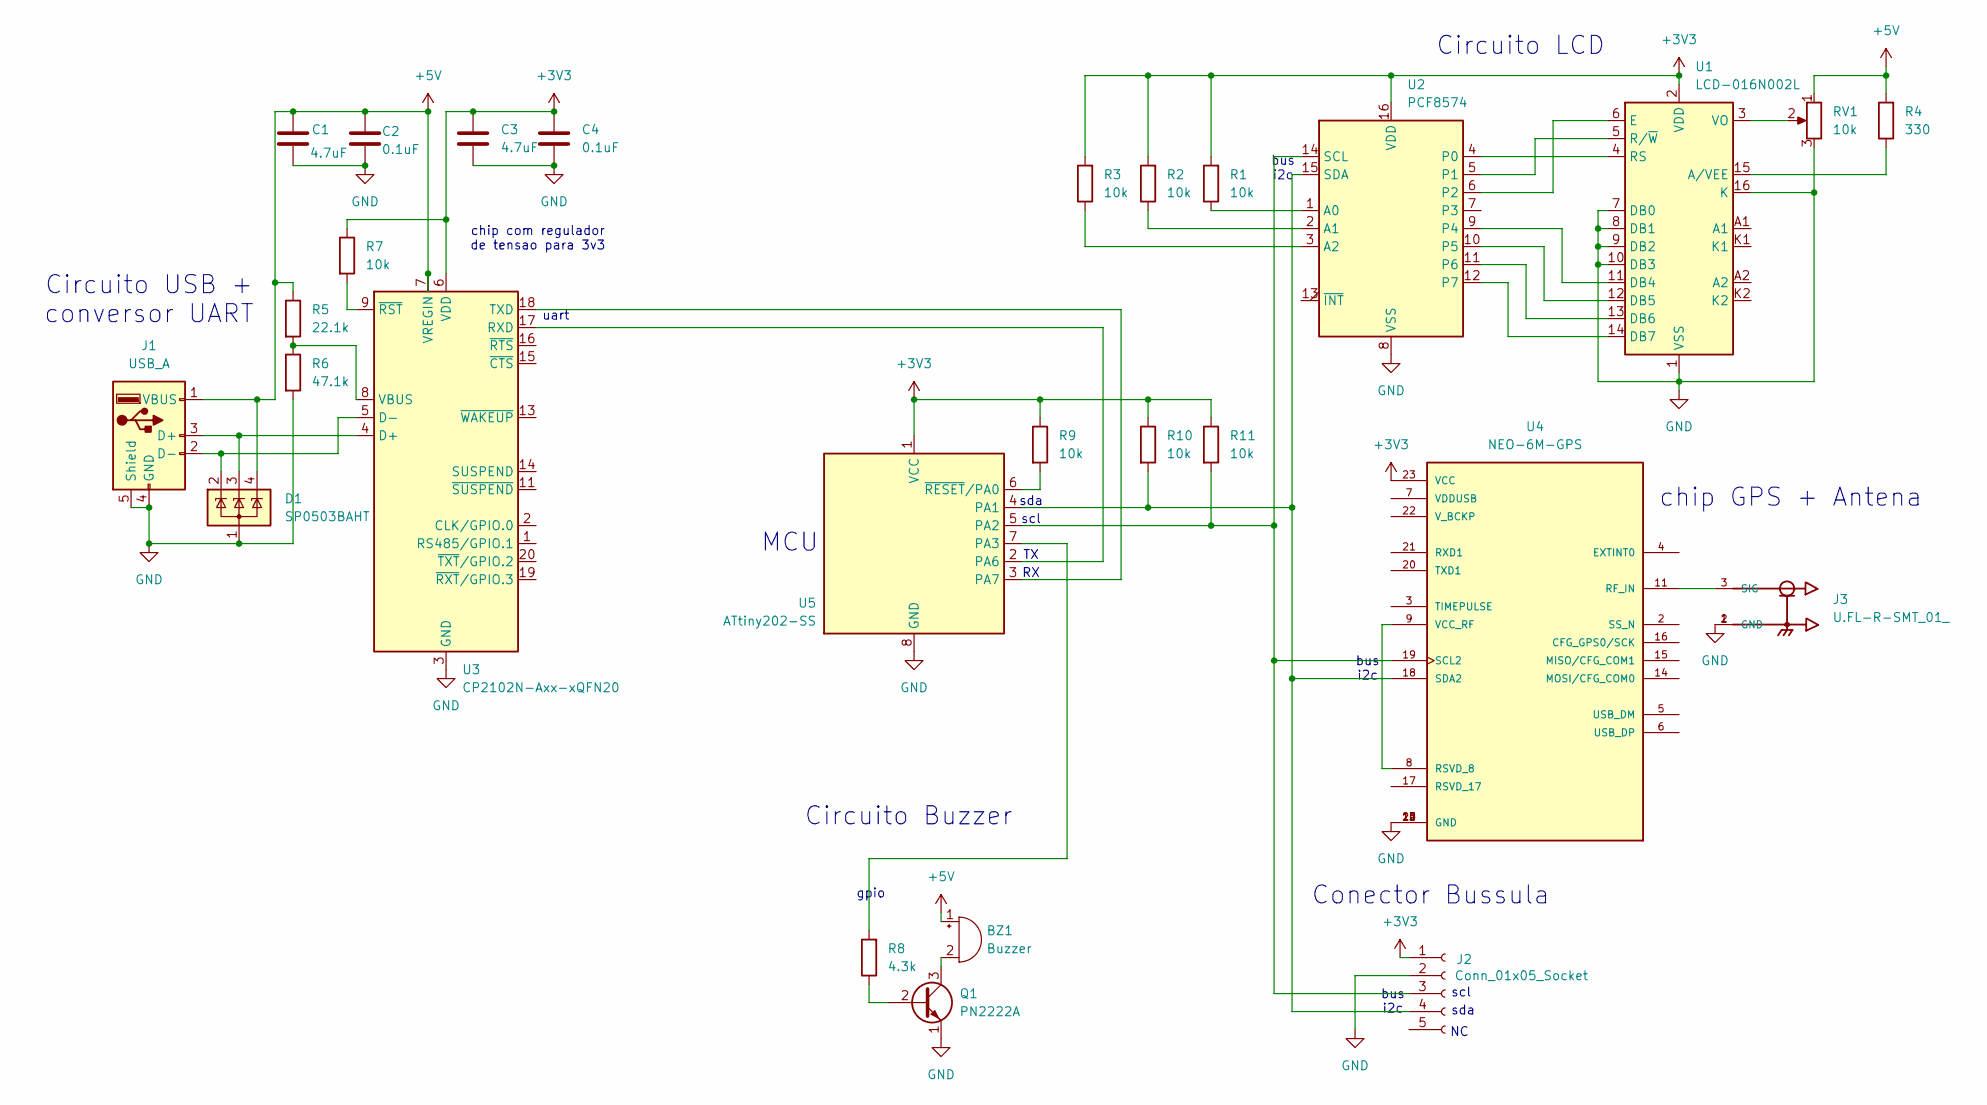
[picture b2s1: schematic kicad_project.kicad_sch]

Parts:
BZ1: Buzzer; Buzzer_12x9.5RM7.6
C1, C3: 4.7uF; C_0402_1005Metric_Pad0.74x0.62mm_HandSolder
C2, C4: 0.1uF; C_0402_1005Metric_Pad0.74x0.62mm_HandSolder
D1: SP0503BAHT; SOT-143
J1: USB_A; USB_A_Receptacle_GCT_USB1046
J2: Conn_01x05_Socket; TE_826576-5_1x05_P3.96mm_Vertical
J3: U.FL-R-SMT_01_; HRS_U.FL-R-SMT_01_
Q1: PN2222A; TO-92_Inline
R1, R2, R3, R7, R9, R10, R11: 10k; R_0402_1005Metric
R4: 330; R_0603_1608Metric_Pad0.98x0.95mm_HandSolder
R5: 22.1k; R_0402_1005Metric
R6: 47.1k; R_0402_1005Metric
R8: 4.3k; R_0402_1005Metric
RV1: 10k; Potentiometer_Bourns_3214G_Horizontal
U1: LCD-016N002L
U2: PCF8574; VQFN-16-1EP_3x3mm_P0.5mm_EP1.8x1.8mm
U3: CP2102N-Axx-xQFN20; QFN-20-1EP_3x3mm_P0.45mm_EP1.6x1.6mm
U4: NEO-6M-GPS; XCVR_NEO-6M-GPS; PARTREV R15
U5: ATtiny202-SS; SOIC-8_3.9x4.9mm_P1.27mm

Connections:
+3V3: C3.1, C4.1, J2.1, R1.2, R2.2, R3.2, R7.1, R9.1, R10.1, R11.1, U1.2 (VDD), U2.16 (VDD), U3.6 (VDD), U4.23 (VCC), U5.1 (VCC)
+5V: BZ1.1 (+), C1.1, C2.1, D1.4 (K), J1.1 (VBUS), R4.2, R5.1, RV1.1, U3.7 (VREGIN)
GND: C1.2, C2.2, C3.2, C4.2, D1.1 (A), J1.4 (GND), J1.5 (Shield), J2.2, J3.1 (GND), J3.2 (GND), Q1.1 (E), R6.2, RV1.3, U1.1 (VSS), U1.7 (DB0), U1.8 (DB1), U1.9 (DB2), U1.10 (DB3), U1.16 (K), U2.8 (VSS), U3.3 (GND), U3.12 (GND), U3.21 (GND), U4.10 (GND), U4.12 (GND), U4.13 (GND), U4.24 (GND), U5.8 (GND)
unnamed: BZ1.2 (-), Q1.3 (C)
unnamed: D1.3 (K), J1.3 (D+), U3.4 (D+)
unnamed: D1.2 (K), J1.2 (D-), U3.5 (D-)
unnamed: J2.3, R11.2, U2.14 (SCL), U4.19 (SCL2), U5.5 (PA2)
unnamed: J2.4, R10.2, U2.15 (SDA), U4.18 (SDA2), U5.4 (PA1)
unnamed: J3.3 (SIG), U4.11 (RF_IN)
unnamed: Q1.2 (B), R8.1
unnamed: R4.1, U1.15 (A/VEE)
unnamed: U1.11 (DB4), U2.9 (P4)
unnamed: U1.12 (DB5), U2.10 (P5)
unnamed: U1.13 (DB6), U2.11 (P6)
unnamed: U1.14 (DB7), U2.12 (P7)
unnamed: U1.6 (E), U2.6 (P2)
unnamed: U1.4 (RS), U2.4 (P0)
unnamed: U1.5 (R/~W), U2.5 (P1)
unnamed: RV1.2, U1.3 (VO)
unnamed: R1.1, U2.1 (A0)
unnamed: R2.1, U2.2 (A1)
unnamed: R3.1, U2.3 (A2)
unnamed: U3.17 (RXD), U5.2 (PA6)
unnamed: U3.18 (TXD), U5.3 (PA7)
unnamed: R5.2, R6.1, U3.8 (VBUS)
unnamed: R7.2, U3.9 (~RST)
unnamed: U4.8 (RSVD_8), U4.9 (VCC_RF)
unnamed: R8.2, U5.7 (PA3)
unnamed: R9.2, U5.6 (~RESET/PA0)

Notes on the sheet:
Circuito LCD
bus i2c
gpio
MCU
chip com regulador de tensao para 3v3
scl
sda
Conector Bussula
chip GPS + Antena
uart
Circuito USB + conversor UART
Circuito Buzzer

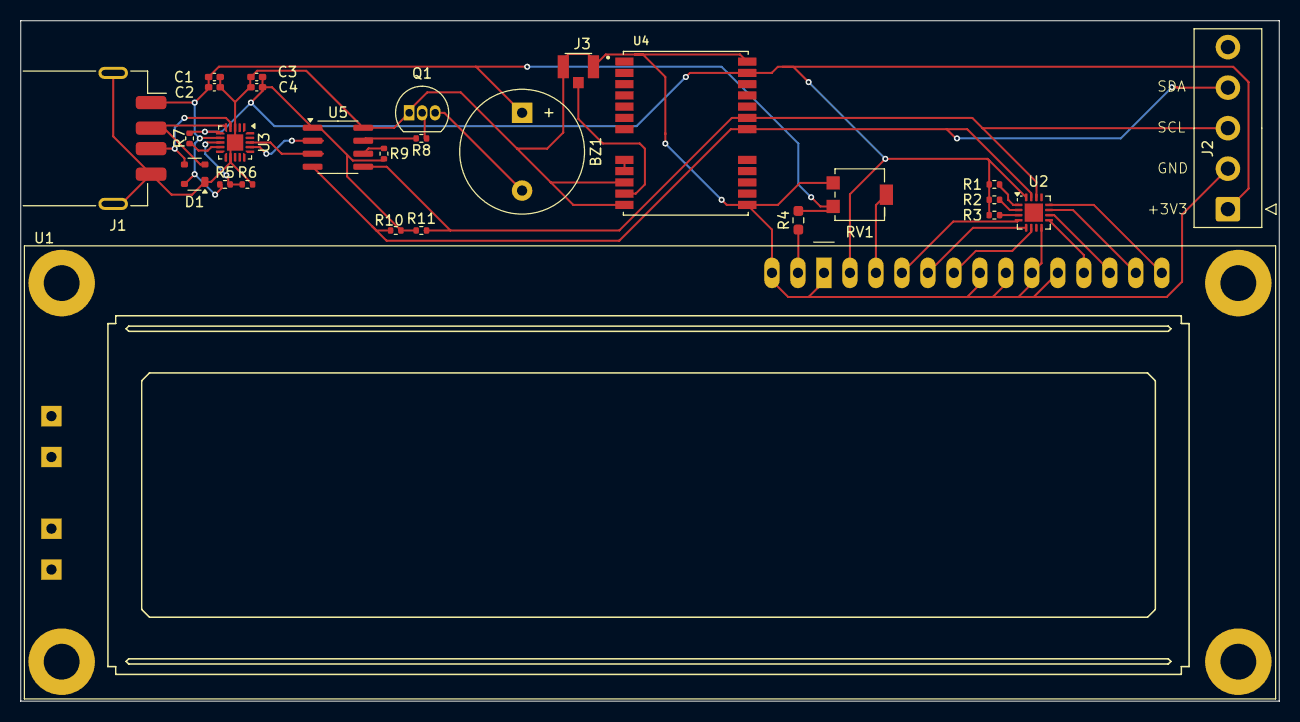
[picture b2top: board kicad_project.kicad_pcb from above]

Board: 2 copper layers, 123.0 x 66.5 mm, 27 parts (0 on the bottom side), 29 nets.

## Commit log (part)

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2024-06-24 Rename projetos/tennistracker/diagrama.svg to projetos/tennistracker/images/diagrama.svg
2024-06-24 Rename projetos/tennistracker/diagrama_estrutural.svg to projetos/tennistracker/images/diagrama_estrutural.svg
2024-06-24 Rename projetos/tennistracker/fluxograma_2.svg to projetos/tennistracker/images/fluxograma_2.svg
2024-06-24 gps e MCU
2024-06-24 roteamento + modelos 3d
2024-06-24 Create gerber
2024-06-24 Atualizando informações E3.md
2024-06-24 Rename projetos/smartfeeder/ESP32-Pinout.jpg to projetos/smartfeeder/images/ESP32-Pinout.jpg
2024-06-24 Rename projetos/smartfeeder/E2 - Algoritmo - comida1.drawio.png to projetos/smartfeeder/images/E3 - Algoritmo - comida1.drawio.png
2024-06-24 Rename projetos/smartfeeder/E2 - algoritmo - água.drawio.png to projetos/smartfeeder/images/E3 - algoritmo - água.drawio.png
2024-06-24 lista dos componentes.md
2024-06-24 Rename projetos/smartfeeder/Smart feeder.png to projetos/smartfeeder/images/Smart feeder.png
2024-06-24 Rename projetos/smartfeeder/bebedouro.drawio.png to projetos/smartfeeder/images/bebedouro.drawio.png
2024-06-24 Rename projetos/smartfeeder/comedouro1.drawio.png to projetos/smartfeeder/images/comedouro1.drawio.png
2024-06-24 Rename projetos/smartfeeder/logo1.png to projetos/smartfeeder/images/logo1.png
2024-06-24 texto no conector da bússula
2024-06-24 atualização dos componentes
2024-06-24 Rename baterai_lr44.pdf to bateria_lr44.pdf
2024-06-24 gerber files
2024-06-24 3d models
2024-06-24 esquema eletrico pdf
2024-06-24 rename to images
2024-06-24 layout pcb pdf
2024-06-24 arquivos drl
2024-06-24 diagramas to imgs
2024-06-24 Adicionado fluxchart_int.drawio
2024-06-24 src_zip
2024-06-24 Adicionado texto de descrição funcional
2024-06-24 Actualizar fluxchart_int.drawio
2024-06-24 Adicionado fluxchart_int.svg
2024-06-24 Actualizar fluxchart_int.svg
2024-06-24 Adicionado texto de descrição estrutural
2024-06-24 mudanças no texto do microcontrolador na parte de descrição estrutural
2024-06-24 update Especificação Estrutural
2024-06-24 atualizacoes em relacao a E2
2024-06-24 Ajustes finais.md
2024-06-24 Rename ImageToStl.com_[pcb]painel_solar_variavel.stl to [PCB]Painel_Solar_Variavel.stl
2024-06-24 add arquivo png da descrição funcional
2024-06-24 mudança de imagem diagrama funcional readme.md
2024-06-24 Finalização.md
2024-06-24 Rename Microcontrolador ATmega48P.pdf to ATmega48P.pdf
2024-06-24 Create datasheets
2024-06-24 Create componentes
2024-06-24 Rename WhatsApp Image 2024-06-24 at 19.10.15.jpeg to lista_componentes
2024-06-25 Rename components.pdf to components.md
2024-06-25 Rename components.md to components.pdf
2024-06-25 READEME
2024-06-25 asasa
2024-06-27 Rename instruções.md to README.md
2024-06-27 Create 3d
2024-06-27 Rename README.md to README.md
2024-06-27 Rename projetos/sistema-controle-de-acesso/images/3d_e_2d.pdf to projetos/sistema-controle-de-acesso/images/images-E3/3d_e_2d.pdf
2024-06-27 Rename controle_acesso.zip to controle_acesso.zip
2024-06-27 Rename projetos/sistema-controle-de-acesso/images/PCB_PCB_controle_acesso_2_2024-06-24.pdf to projetos/sistema-controle-de-acesso/images/images-E3/PCB_PCB_controle_acesso_2_2024-06-24.pdf
2024-06-27 Rename projetos/sistema-controle-de-acesso/images/Schematic_controle-de-acesso_2024-06-24.png to projetos/sistema-controle-de-acesso/images/images-E3/Schematic_controle-de-acesso_2024-06-24.png
2024-06-27 Rename projetos/sistema-controle-de-acesso/images/Schematic_controle_acesso.pdf to projetos/sistema-controle-de-acesso/images/images-E3/Schematic_controle_acesso.pdf
2024-06-27 Rename projetos/sistema-controle-de-acesso/images/componentes to projetos/sistema-controle-de-acesso/images/images-E3/componentes
2024-06-27 Rename projetos/sistema-controle-de-acesso/images/lista_componentes to projetos/sistema-controle-de-acesso/images/images-E3/lista_componentes
2024-06-27 Rename projetos/sistema-controle-de-acesso/images/Captura_de_Imagem.drawio.svg to projetos/sistema-controle-de-acesso/images/images-E2/Captura_de_Imagem.drawio.svg
2024-06-27 Rename projetos/sistema-controle-de-acesso/images/Diagrama_Funcional.drawio.svg to projetos/sistema-controle-de-acesso/images/images-E2/Diagrama_Funcional.drawio.svg
2024-06-27 Rename projetos/sistema-controle-de-acesso/images/Feedback_Sonoro.drawio.svg to projetos/sistema-controle-de-acesso/images/images-E2/Feedback_Sonoro.drawio.svg
2024-06-27 Rename projetos/sistema-controle-de-acesso/images/Inicializacao_do_Sistema.drawio.svg to projetos/sistema-controle-de-acesso/images/images-E2/Inicializacao_do_Sistema.drawio.svg
2024-06-27 Rename projetos/sistema-controle-de-acesso/images/Leitura_de_QR_Code.drawio.svg to projetos/sistema-controle-de-acesso/images/images-E2/Leitura_de_QR_Code.drawio.svg
2024-06-27 Rename projetos/sistema-controle-de-acesso/images/Processamento_de_Imagem.drawio.svg to projetos/sistema-controle-de-acesso/images/images-E2/Processamento_de_Imagem.drawio.svg
2024-06-27 Rename projetos/sistema-controle-de-acesso/images/Processamento_de_QR_Code.drawio.svg to projetos/sistema-controle-de-acesso/images/images-E2/Processamento_de_QR_Code.drawio.svg
2024-06-27 Rename projetos/sistema-controle-de-acesso/images/Untitled Diagram.drawio.png to projetos/sistema-controle-de-acesso/images/images-E2/InicializacaoDeSistema.drawio.png
2024-06-27 Rename projetos/sistema-controle-de-acesso/images/Diagrama_acesso.drawio to projetos/sistema-controle-de-acesso/images/images-E1/Diagrama_acesso.drawio
2024-06-27 Rename projetos/sistema-controle-de-acesso/images/Diagrama_acesso.drawio.svg to projetos/sistema-controle-de-acesso/images/images-E1/Diagrama_acesso.drawio.svg
2024-06-27 Rename projetos/sistema-controle-de-acesso/images/diagrama1.drawio.svg to projetos/sistema-controle-de-acesso/images/images-E1/diagrama1.drawio.svg
2024-06-28 Rename projetos/sistema-controle-de-acesso/datasheets/Mysentech-MC12G_EN_translation_22_June_2024.pdf to projetos/sistema-controle-de-acesso/datasheets/sensor-de-presenca/Mysentech-MC12G_EN_translati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
2024-06-28 Rename projetos/sistema-controle-de-acesso/datasheets/Mysentech-MC12G_EN_translation_22_June_2024.docx to projetos/sistema-controle-de-acesso/datasheets/sensor-de-presenca/Mysentech-MC12G_EN_translat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
2024-06-28 Rename projetos/sistema-controle-de-acesso/datasheets/README.md to projetos/sistema-controle-de-acesso/datasheets/sensor-de-presenca/README.md
2024-06-28 Rename projetos/sistema-controle-de-acesso/datasheets/Mysentech-MC12GPCB-EN-24_Jun-2024.pdf to projetos/sistema-controle-de-acesso/datasheets/sensor-de-presenca/Mysentech-MC12GPCB-EN-24_Jun-2024.pdf
2024-06-28 Rename projetos/sistema-controle-de-acesso/datasheets/LICENSE to projetos/sistema-controle-de-acesso/datasheets/sensor-de-presenca/LICENSE
2024-07-01 Revert "Monitoramento"
